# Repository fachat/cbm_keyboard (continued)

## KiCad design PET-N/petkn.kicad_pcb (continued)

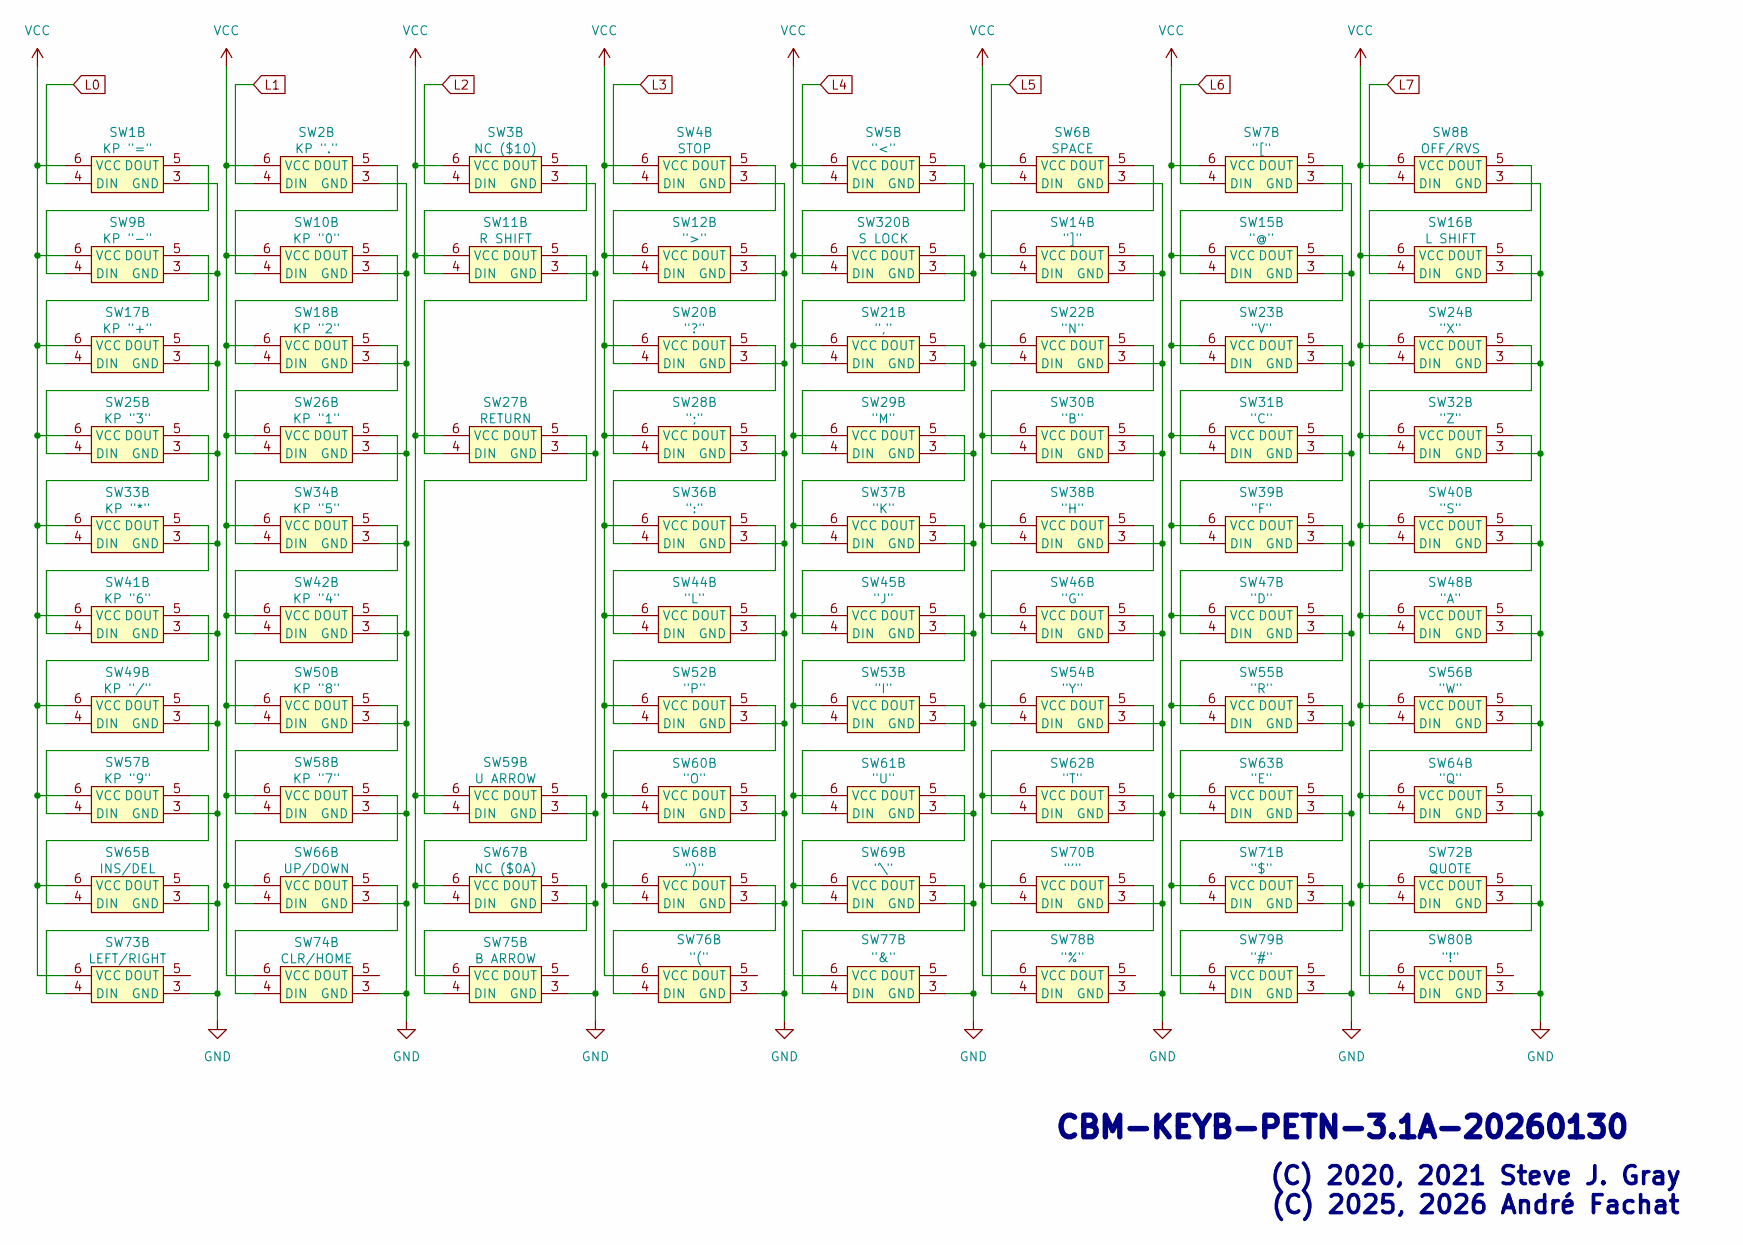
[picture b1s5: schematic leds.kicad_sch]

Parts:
SW1: KP "="; SW_Cherry_MX_1.00u_PCB_with_RGB_LED
SW2: KP "."; SW_Cherry_MX_1.00u_PCB_with_RGB_LED
SW3: NC ($10); SW_Cherry_MX_1.25u_PCB_with_RGB_LED
SW4: STOP; SW_Cherry_MX_1.00u_PCB_with_RGB_LED
SW5: "<"; SW_Cherry_MX_1.00u_PCB_with_RGB_LED
SW6: SPACE; SW_Cherry_MX_6.25u_PCB_with_RGB_LED
SW7: "["; SW_Cherry_MX_1.00u_PCB_with_RGB_LED
SW8: OFF/RVS; SW_Cherry_MX_1.50u_PCB_with_RGB_LED
SW9: KP "-"; SW_Cherry_MX_1.00u_PCB_with_RGB_LED
SW10: KP "0"; SW_Cherry_MX_1.00u_PCB_with_RGB_LED
SW11: R SHIFT; SW_Cherry_MX_2.00u_PCB_with_RGB_LED
SW12: ">"; SW_Cherry_MX_1.00u_PCB_with_RGB_LED
SW14: "]"; SW_Cherry_MX_1.00u_PCB_with_RGB_LED
SW15: "@"; SW_Cherry_MX_1.00u_PCB_with_RGB_LED
SW16: L SHIFT; SW_Cherry_MX_2.00u_PCB_with_RGB_LED
SW17: KP "+"; SW_Cherry_MX_1.00u_PCB_with_RGB_LED
SW18: KP "2"; SW_Cherry_MX_1.00u_PCB_with_RGB_LED
SW20: "?"; SW_Cherry_MX_1.00u_PCB_with_RGB_LED
SW21: ","; SW_Cherry_MX_1.00u_PCB_with_RGB_LED
SW22: "N"; SW_Cherry_MX_1.00u_PCB_with_RGB_LED
SW23: "V"; SW_Cherry_MX_1.00u_PCB_with_RGB_LED
SW24: "X"; SW_Cherry_MX_1.00u_PCB_with_RGB_LED
SW25: KP "3"; SW_Cherry_MX_1.00u_PCB_with_RGB_LED
SW26: KP "1"; SW_Cherry_MX_1.00u_PCB_with_RGB_LED
SW27: RETURN; SW_Cherry_MX_1.50u_PCB_with_RGB_LED
SW28: ";"; SW_Cherry_MX_1.00u_PCB_with_RGB_LED
SW29: "M"; SW_Cherry_MX_1.00u_PCB_with_RGB_LED
SW30: "B"; SW_Cherry_MX_1.00u_PCB_with_RGB_LED
SW31: "C"; SW_Cherry_MX_1.00u_PCB_with_RGB_LED
SW32: "Z"; SW_Cherry_MX_1.00u_PCB_with_RGB_LED
SW33: KP "*"; SW_Cherry_MX_1.00u_PCB_with_RGB_LED
SW34: KP "5"; SW_Cherry_MX_1.00u_PCB_with_RGB_LED
SW36: ":"; SW_Cherry_MX_1.00u_PCB_with_RGB_LED
SW37: "K"; SW_Cherry_MX_1.00u_PCB_with_RGB_LED
SW38: "H"; SW_Cherry_MX_1.00u_PCB_with_RGB_LED
SW39: "F"; SW_Cherry_MX_1.00u_PCB_with_RGB_LED
SW40: "S"; SW_Cherry_MX_1.00u_PCB_with_RGB_LED
SW41: KP "6"; SW_Cherry_MX_1.00u_PCB_with_RGB_LED
SW42: KP "4"; SW_Cherry_MX_1.00u_PCB_with_RGB_LED
SW44: "L"; SW_Cherry_MX_1.00u_PCB_with_RGB_LED
SW45: "J"; SW_Cherry_MX_1.00u_PCB_with_RGB_LED
SW46: "G"; SW_Cherry_MX_1.00u_PCB_with_RGB_LED
SW47: "D"; SW_Cherry_MX_1.00u_PCB_with_RGB_LED
SW48: "A"; SW_Cherry_MX_1.00u_PCB_with_RGB_LED
SW49: KP "/"; SW_Cherry_MX_1.00u_PCB_with_RGB_LED
SW50: KP "8"; SW_Cherry_MX_1.00u_PCB_with_RGB_LED
SW52: "P"; SW_Cherry_MX_1.00u_PCB_with_RGB_LED
SW53: "I"; SW_Cherry_MX_1.00u_PCB_with_RGB_LED
SW54: "Y"; SW_Cherry_MX_1.00u_PCB_with_RGB_LED
SW55: "R"; SW_Cherry_MX_1.00u_PCB_with_RGB_LED
SW56: "W"; SW_Cherry_MX_1.00u_PCB_with_RGB_LED
SW57: KP "9"; SW_Cherry_MX_1.00u_PCB_with_RGB_LED
SW58: KP "7"; SW_Cherry_MX_1.00u_PCB_with_RGB_LED
SW59: U ARROW; SW_Cherry_MX_1.00u_PCB_with_RGB_LED
SW60: "O"; SW_Cherry_MX_1.00u_PCB_with_RGB_LED
SW61: "U"; SW_Cherry_MX_1.00u_PCB_with_RGB_LED
SW62: "T"; SW_Cherry_MX_1.00u_PCB_with_RGB_LED
SW63: "E"; SW_Cherry_MX_1.00u_PCB_with_RGB_LED
SW64: "Q"; SW_Cherry_MX_1.00u_PCB_with_RGB_LED
SW65: INS/DEL; SW_Cherry_MX_1.00u_PCB_with_RGB_LED
SW66: UP/DOWN; SW_Cherry_MX_1.00u_PCB_with_RGB_LED
SW67: NC ($0A); SW_Cherry_MX_1.50u_PCB_with_RGB_LED
SW68: ")"; SW_Cherry_MX_1.00u_PCB_with_RGB_LED
SW69: "\"; SW_Cherry_MX_1.00u_PCB_with_RGB_LED
SW70: "'"; SW_Cherry_MX_1.00u_PCB_with_RGB_LED
SW71: "$"; SW_Cherry_MX_1.00u_PCB_with_RGB_LED
SW72: QUOTE; SW_Cherry_MX_1.00u_PCB_with_RGB_LED
SW73: LEFT/RIGHT; SW_Cherry_MX_1.00u_PCB_with_RGB_LED
SW74: CLR/HOME; SW_Cherry_MX_1.00u_PCB_with_RGB_LED
SW75: B ARROW; SW_Cherry_MX_1.00u_PCB_with_RGB_LED
SW76: "("; SW_Cherry_MX_1.00u_PCB_with_RGB_LED
SW77: "&"; SW_Cherry_MX_1.00u_PCB_with_RGB_LED
SW78: "%"; SW_Cherry_MX_1.00u_PCB_with_RGB_LED
SW79: "#"; SW_Cherry_MX_1.00u_PCB_with_RGB_LED
SW80: "!"; SW_Cherry_MX_1.00u_PCB_with_RGB_LED
SW320: S LOCK; SW_Cherry_MX_1.50u_PCB_with_RGB_LED

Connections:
GND: SW1.3 (GND), SW2.3 (GND), SW3.3 (GND), SW4.3 (GND), SW5.3 (GND), SW6.3 (GND), SW7.3 (GND), SW8.3 (GND), SW9.3 (GND), SW10.3 (GND), SW11.3 (GND), SW12.3 (GND), SW14.3 (GND), SW15.3 (GND), SW16.3 (GND), SW17.3 (GND), SW18.3 (GND), SW20.3 (GND), SW21.3 (GND), SW22.3 (GND), SW23.3 (GND), SW24.3 (GND), SW25.3 (GND), SW26.3 (GND), SW27.3 (GND), SW28.3 (GND), SW29.3 (GND), SW30.3 (GND), SW31.3 (GND), SW32.3 (GND), SW33.3 (GND), SW34.3 (GND), SW36.3 (GND), SW37.3 (GND), SW38.3 (GND), SW39.3 (GND), SW40.3 (GND), SW41.3 (GND), SW42.3 (GND), SW44.3 (GND), SW45.3 (GND), SW46.3 (GND), SW47.3 (GND), SW48.3 (GND), SW49.3 (GND), SW50.3 (GND), SW52.3 (GND), SW53.3 (GND), SW54.3 (GND), SW55.3 (GND), SW56.3 (GND), SW57.3 (GND), SW58.3 (GND), SW59.3 (GND), SW60.3 (GND), SW61.3 (GND), SW62.3 (GND), SW63.3 (GND), SW64.3 (GND), SW65.3 (GND), SW66.3 (GND), SW67.3 (GND), SW68.3 (GND), SW69.3 (GND), SW70.3 (GND), SW71.3 (GND), SW72.3 (GND), SW73.3 (GND), SW74.3 (GND), SW75.3 (GND), SW76.3 (GND), SW77.3 (GND), SW78.3 (GND), SW79.3 (GND), SW80.3 (GND), SW320.3 (GND); also elsewhere on the board
L0: SW1.4 (DIN); also elsewhere on the board
L1: SW2.4 (DIN); also elsewhere on the board
L2: SW3.4 (DIN); also elsewhere on the board
L3: SW4.4 (DIN); also elsewhere on the board
L4: SW5.4 (DIN); also elsewhere on the board
L5: SW6.4 (DIN); also elsewhere on the board
L6: SW7.4 (DIN); also elsewhere on the board
L7: SW8.4 (DIN); also elsewhere on the board
unnamed: SW1.5 (DOUT), SW9.4 (DIN)
unnamed: SW2.5 (DOUT), SW10.4 (DIN)
unnamed: SW10.5 (DOUT), SW18.4 (DIN)
unnamed: SW3.5 (DOUT), SW11.4 (DIN)
unnamed: SW11.5 (DOUT), SW27.4 (DIN)
unnamed: SW4.5 (DOUT), SW12.4 (DIN)
unnamed: SW12.5 (DOUT), SW20.4 (DIN)
unnamed: SW6.5 (DOUT), SW14.4 (DIN)
unnamed: SW14.5 (DOUT), SW22.4 (DIN)
unnamed: SW7.5 (DOUT), SW15.4 (DIN)
unnamed: SW15.5 (DOUT), SW23.4 (DIN)
unnamed: SW8.5 (DOUT), SW16.4 (DIN)
unnamed: SW16.5 (DOUT), SW24.4 (DIN)
unnamed: SW9.5 (DOUT), SW17.4 (DIN)
unnamed: SW17.5 (DOUT), SW25.4 (DIN)
unnamed: SW18.5 (DOUT), SW26.4 (DIN)
unnamed: SW20.5 (DOUT), SW28.4 (DIN)
unnamed: SW21.4 (DIN), SW320.5 (DOUT)
unnamed: SW21.5 (DOUT), SW29.4 (DIN)
unnamed: SW22.5 (DOUT), SW30.4 (DIN)
unnamed: SW23.5 (DOUT), SW31.4 (DIN)
unnamed: SW24.5 (DOUT), SW32.4 (DIN)
unnamed: SW25.5 (DOUT), SW33.4 (DIN)
unnamed: SW26.5 (DOUT), SW34.4 (DIN)
unnamed: SW27.5 (DOUT), SW59.4 (DIN)
unnamed: SW28.5 (DOUT), SW36.4 (DIN)
unnamed: SW29.5 (DOUT), SW37.4 (DIN)
unnamed: SW30.5 (DOUT), SW38.4 (DIN)
unnamed: SW31.5 (DOUT), SW39.4 (DIN)
unnamed: SW32.5 (DOUT), SW40.4 (DIN)
unnamed: SW33.5 (DOUT), SW41.4 (DIN)
unnamed: SW34.5 (DOUT), SW42.4 (DIN)
unnamed: SW36.5 (DOUT), SW44.4 (DIN)
unnamed: SW37.5 (DOUT), SW45.4 (DIN)
unnamed: SW38.5 (DOUT), SW46.4 (DIN)
unnamed: SW39.5 (DOUT), SW47.4 (DIN)
unnamed: SW40.5 (DOUT), SW48.4 (DIN)
unnamed: SW41.5 (DOUT), SW49.4 (DIN)
unnamed: SW42.5 (DOUT), SW50.4 (DIN)
unnamed: SW44.5 (DOUT), SW52.4 (DIN)
unnamed: SW45.5 (DOUT), SW53.4 (DIN)
unnamed: SW46.5 (DOUT), SW54.4 (DIN)
unnamed: SW47.5 (DOUT), SW55.4 (DIN)
unnamed: SW48.5 (DOUT), SW56.4 (DIN)
unnamed: SW49.5 (DOUT), SW57.4 (DIN)
unnamed: SW50.5 (DOUT), SW58.4 (DIN)
unnamed: SW52.5 (DOUT), SW60.4 (DIN)
unnamed: SW53.5 (DOUT), SW61.4 (DIN)
unnamed: SW54.5 (DOUT), SW62.4 (DIN)
unnamed: SW55.5 (DOUT), SW63.4 (DIN)
unnamed: SW56.5 (DOUT), SW64.4 (DIN)
unnamed: SW57.5 (DOUT), SW65.4 (DIN)
unnamed: SW58.5 (DOUT), SW66.4 (DIN)
unnamed: SW59.5 (DOUT), SW67.4 (DIN)
unnamed: SW60.5 (DOUT), SW68.4 (DIN)
unnamed: SW61.5 (DOUT), SW69.4 (DIN)
unnamed: SW62.5 (DOUT), SW70.4 (DIN)
unnamed: SW63.5 (DOUT), SW71.4 (DIN)
unnamed: SW64.5 (DOUT), SW72.4 (DIN)
unnamed: SW65.5 (DOUT), SW73.4 (DIN)
unnamed: SW66.5 (DOUT), SW74.4 (DIN)
unnamed: SW67.5 (DOUT), SW75.4 (DIN)
unnamed: SW68.5 (DOUT), SW76.4 (DIN)
unnamed: SW69.5 (DOUT), SW77.4 (DIN)
unnamed: SW70.5 (DOUT), SW78.4 (DIN)
unnamed: SW71.5 (DOUT), SW79.4 (DIN)
unnamed: SW72.5 (DOUT), SW80.4 (DIN)
unnamed: SW5.5 (DOUT), SW320.4 (DIN)
VCC: SW1.6 (VCC), SW2.6 (VCC), SW3.6 (VCC), SW4.6 (VCC), SW5.6 (VCC), SW6.6 (VCC), SW7.6 (VCC), SW8.6 (VCC), SW9.6 (VCC), SW10.6 (VCC), SW11.6 (VCC), SW12.6 (VCC), SW14.6 (VCC), SW15.6 (VCC), SW16.6 (VCC), SW17.6 (VCC), SW18.6 (VCC), SW20.6 (VCC), SW21.6 (VCC), SW22.6 (VCC), SW23.6 (VCC), SW24.6 (VCC), SW25.6 (VCC), SW26.6 (VCC), SW27.6 (VCC), SW28.6 (VCC), SW29.6 (VCC), SW30.6 (VCC), SW31.6 (VCC), SW32.6 (VCC), SW33.6 (VCC), SW34.6 (VCC), SW36.6 (VCC), SW37.6 (VCC), SW38.6 (VCC), SW39.6 (VCC), SW40.6 (VCC), SW41.6 (VCC), SW42.6 (VCC), SW44.6 (VCC), SW45.6 (VCC), SW46.6 (VCC), SW47.6 (VCC), SW48.6 (VCC), SW49.6 (VCC), SW50.6 (VCC), SW52.6 (VCC), SW53.6 (VCC), SW54.6 (VCC), SW55.6 (VCC), SW56.6 (VCC), SW57.6 (VCC), SW58.6 (VCC), SW59.6 (VCC), SW60.6 (VCC), SW61.6 (VCC), SW62.6 (VCC), SW63.6 (VCC), SW64.6 (VCC), SW65.6 (VCC), SW66.6 (VCC), SW67.6 (VCC), SW68.6 (VCC), SW69.6 (VCC), SW70.6 (VCC), SW71.6 (VCC), SW72.6 (VCC), SW73.6 (VCC), SW74.6 (VCC), SW75.6 (VCC), SW76.6 (VCC), SW77.6 (VCC), SW78.6 (VCC), SW79.6 (VCC), SW80.6 (VCC), SW320.6 (VCC); also elsewhere on the board

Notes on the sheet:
CBM-KEYB-PETN-3.1A-20260130
(C) 2020, 2021 Steve J. Gray (C) 2025, 2026 André Fachat

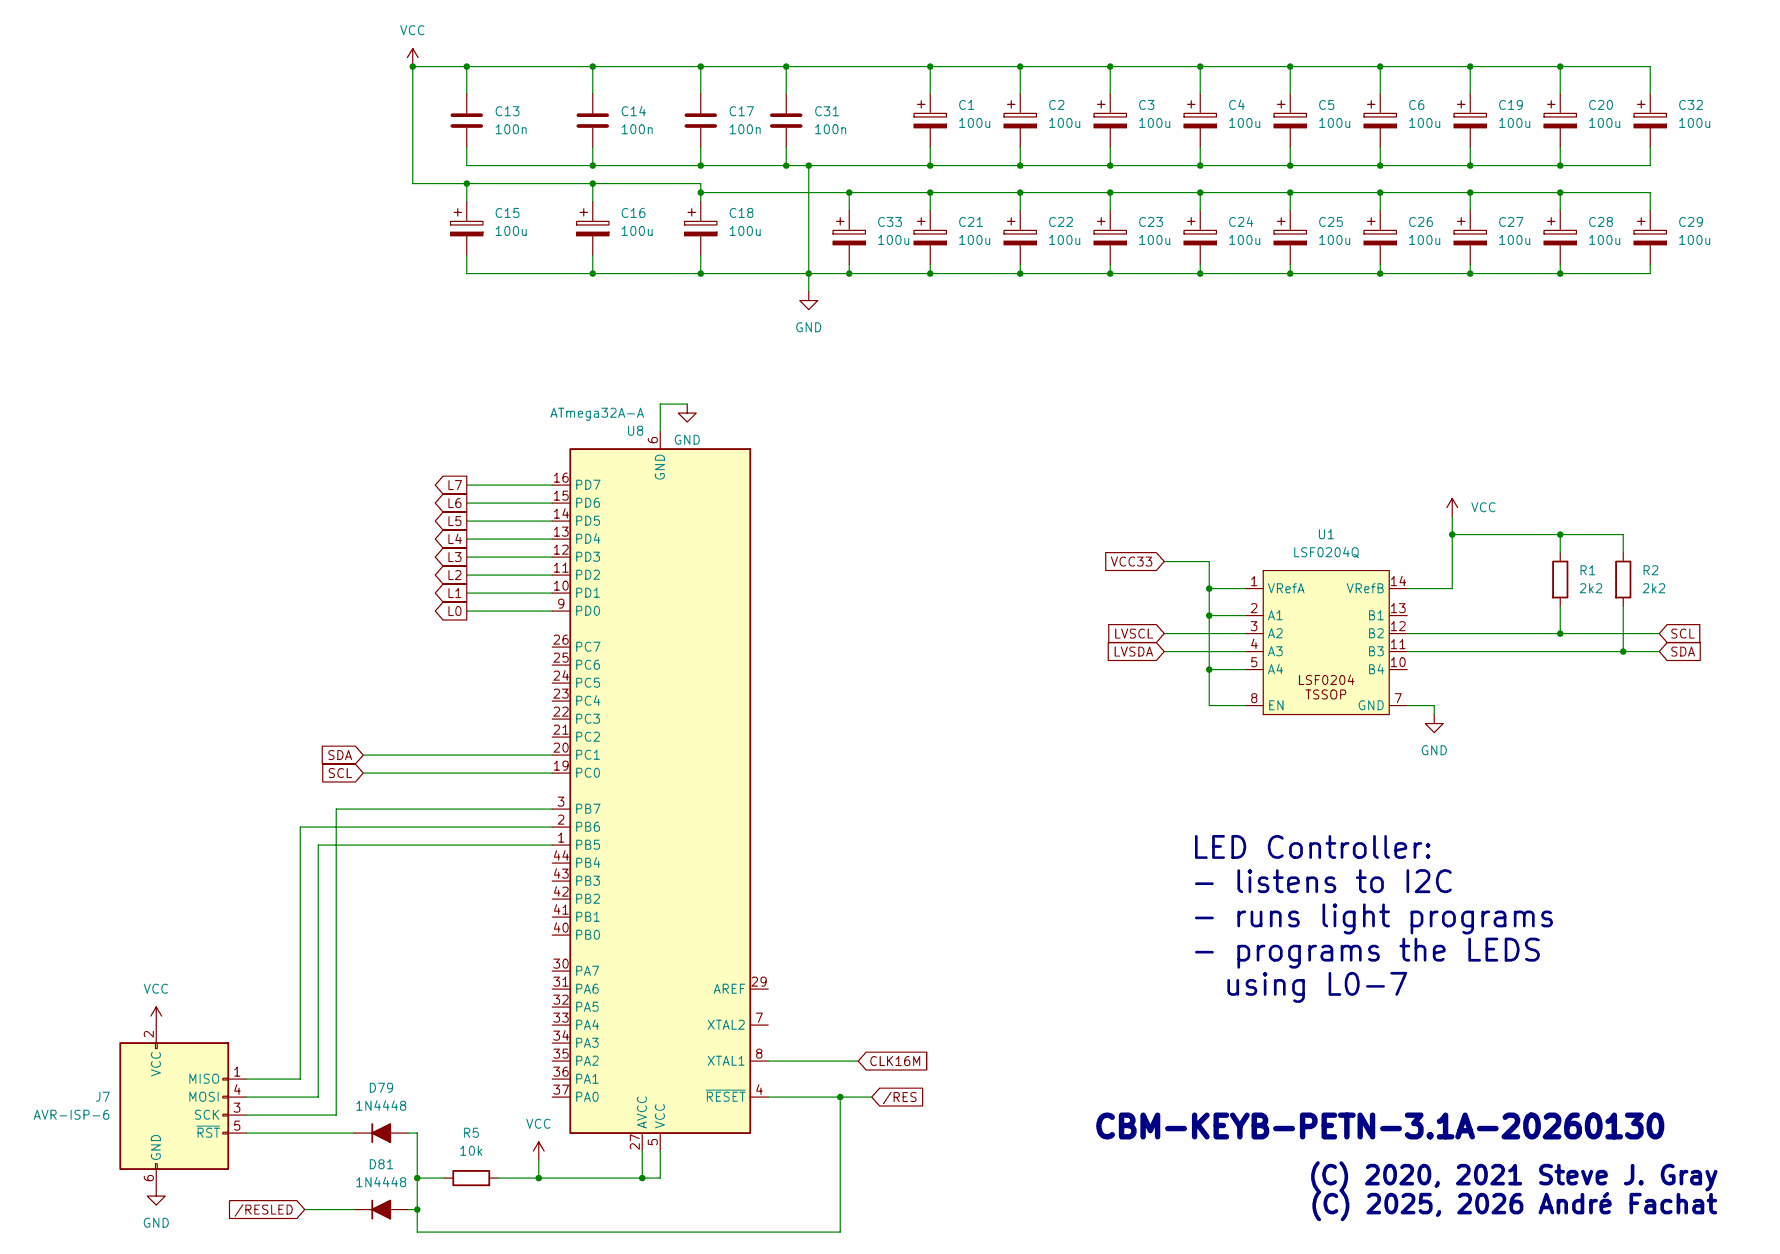
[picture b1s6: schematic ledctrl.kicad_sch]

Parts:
C1, C2, C3, C4, C5, C6, C15, C16, C18, C19, C20, C21, C22, C23, C24, C25, C26, C27, C28, C29, C32, C33: 100u; C_1206_3216Metric_Pad1.33x1.80mm_HandSolder; LCSC C15008
C13, C14, C17, C31: 100n; C_0805_2012Metric_Pad1.18x1.45mm_HandSolder; LCSC C14663
D79, D81: 1N4448; D_SOD-323_HandSoldering
J7: AVR-ISP-6; IDC-Header_2x03_P2.54mm_Vertical; LCSC C5372863
R1, R2: 2k2; R_0603_1608Metric
R5: 10k; R_0603_1608Metric
U1: LSF0204Q; TSSOP-14_4.4x5mm_P0.65mm; LCSC C2677502
U8: ATmega32A-A; TQFP-44_10x10mm_P0.8mm; LCSC C5659

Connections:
CLK16M: U8.8 (XTAL1); also elsewhere on the board
GND: C1.2, C2.2, C3.2, C4.2, C5.2, C6.2, C13.2, C14.2, C15.2, C16.2, C17.2, C18.2, C19.2, C20.2, C21.2, C22.2, C23.2, C24.2, C25.2, C26.2, C27.2, C28.2, C29.2, C31.2, C32.2, C33.2, J7.6 (GND), U1.7 (GND), U8.6 (GND), U8.18 (GND), U8.28 (GND), U8.39 (GND); also elsewhere on the board
L0: U8.9 (PD0); also elsewhere on the board
L1: U8.10 (PD1); also elsewhere on the board
L2: U8.11 (PD2); also elsewhere on the board
L3: U8.12 (PD3); also elsewhere on the board
L4: U8.13 (PD4); also elsewhere on the board
L5: U8.14 (PD5); also elsewhere on the board
L6: U8.15 (PD6); also elsewhere on the board
L7: U8.16 (PD7); also elsewhere on the board
LVSCL: U1.3 (A2); also elsewhere on the board
LVSDA: U1.4 (A3); also elsewhere on the board
unnamed: D79.1 (K), J7.5 (~RST)
unnamed: J7.1 (MISO), U8.2 (PB6)
unnamed: J7.4 (MOSI), U8.1 (PB5)
unnamed: J7.3 (SCK), U8.3 (PB7)
SCL: R1.2, U1.12 (B2), U8.19 (PC0); also elsewhere on the board
SDA: R2.2, U1.11 (B3), U8.20 (PC1); also elsewhere on the board
VCC: C1.1, C2.1, C3.1, C4.1, C5.1, C6.1, C13.1, C14.1, C15.1, C16.1, C17.1, C18.1, C19.1, C20.1, C21.1, C22.1, C23.1, C24.1, C25.1, C26.1, C27.1, C28.1, C29.1, C31.1, C32.1, C33.1, J7.2 (VCC), R1.1, R2.1, R5.2, U1.14 (VRefB), U8.5 (VCC), U8.17 (VCC), U8.27 (AVCC), U8.38 (VCC); also elsewhere on the board
VCC33: U1.1 (VRefA), U1.2 (A1), U1.5 (A4), U1.8 (EN); also elsewhere on the board
cR1: D79.2 (A), D81.2 (A), R5.1, U8.4 (~RESET); also elsewhere on the board
/RESLED: D81.1 (K); also elsewhere on the board

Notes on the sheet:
(C) 2020, 2021 Steve J. Gray (C) 2025, 2026 André Fachat
CBM-KEYB-PETN-3.1A-20260130
LED Controller: - listens to I2C - runs light programs - programs the LEDS using L0-7

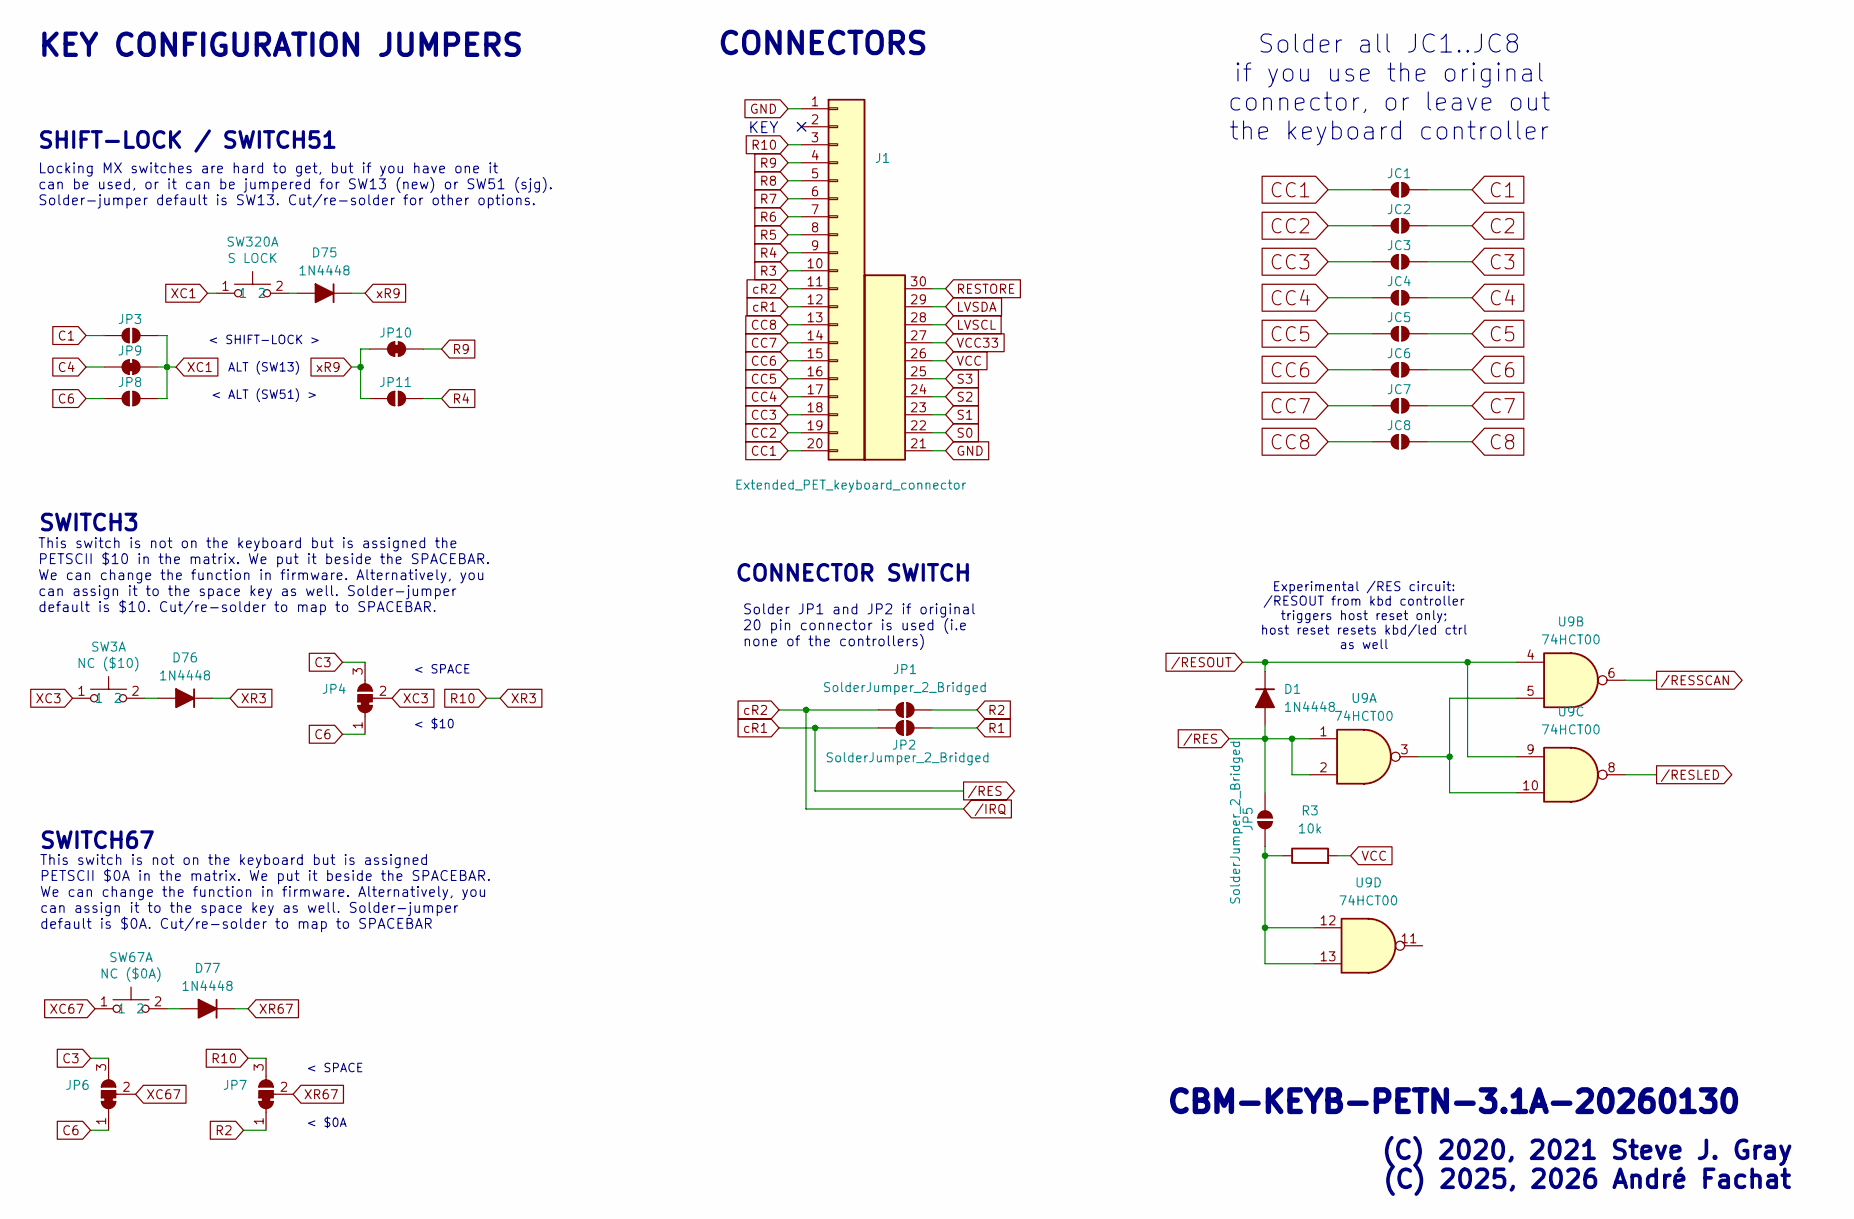
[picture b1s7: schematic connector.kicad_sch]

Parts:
D1, D75, D76, D77: 1N4448; D_SOD-323_HandSoldering
J1: Extended_PET_keyboard_connector; PET_Extended_Keyboard_Connector
JC1, JC2, JC3, JC4, JC5, JC6, JC7, JC8: SolderJumper_2_Bridged; SolderJumper-2_P1.3mm_Open_RoundedPad1.0x1.5mm
JP1, JP2, JP3, JP5, JP8, JP11: SolderJumper_2_Bridged; SolderJumper-2_P1.3mm_Open_RoundedPad1.0x1.5mm
JP4, JP6, JP7: SolderJumper_3_Bridged12; SolderJumper-3_P1.3mm_Bridged12_RoundedPad1.0x1.5mm_NumberL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
JP9, JP10: SolderJumper_2_Bridged; SolderJumper-2_P1.3mm_Bridged_RoundedPad1.0x1.5mm
R3: 10k; R_0603_1608Metric
SW3: NC ($10); SW_Cherry_MX_1.25u_PCB_with_RGB_LED
SW67: NC ($0A); SW_Cherry_MX_1.50u_PCB_with_RGB_LED
SW320: S LOCK; SW_Cherry_MX_1.50u_PCB_with_RGB_LED
U9: 74HCT00; SOIC-14_3.9x8.7mm_P1.27mm

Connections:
C1: JC1.2 (B), JP3.1 (A); also elsewhere on the board
C2: JC2.2 (B); also elsewhere on the board
C3: JC3.2 (B), JP4.3 (B), JP6.3 (B); also elsewhere on the board
C4: JC4.2 (B), JP9.1 (A); also elsewhere on the board
C5: JC5.2 (B); also elsewhere on the board
C6: JC6.2 (B), JP4.1 (A), JP6.1 (A), JP8.1 (A); also elsewhere on the board
C7: JC7.2 (B); also elsewhere on the board
C8: JC8.2 (B); also elsewhere on the board
CC1: J1.20 (C1), JC1.1 (A); also elsewhere on the board
CC2: J1.19 (C2), JC2.1 (A); also elsewhere on the board
CC3: J1.18 (C3), JC3.1 (A); also elsewhere on the board
CC4: J1.17 (C4), JC4.1 (A); also elsewhere on the board
CC5: J1.16 (C5), JC5.1 (A); also elsewhere on the board
CC6: J1.15 (C6), JC6.1 (A); also elsewhere on the board
CC7: J1.14 (C7), JC7.1 (A); also elsewhere on the board
CC8: J1.13 (C8), JC8.1 (A); also elsewhere on the board
GND: J1.1 (GND), J1.21 (GND); also elsewhere on the board
LVSCL: J1.28 (SCL); also elsewhere on the board
LVSDA: J1.29 (SCA); also elsewhere on the board
unnamed: D75.2 (A), SW320.2
unnamed: D76.2 (A), SW3.2
unnamed: D77.2 (A), SW67.2
unnamed: JP5.2 (B), R3.1, U9.12, U9.13
unnamed: U9.3, U9.5, U9.10
R1: JP2.2 (B); also elsewhere on the board
R2: JP1.2 (B), JP7.1 (A); also elsewhere on the board
R3: J1.10 (R3); also elsewhere on the board
R4: J1.9 (R4), JP11.2 (B); also elsewhere on the board
R5: J1.8 (R5); also elsewhere on the board
R6: J1.7 (R6); also elsewhere on the board
R7: J1.6 (R7); also elsewhere on the board
R8: J1.5 (R8); also elsewhere on the board
R9: J1.4 (R9), JP10.2 (B); also elsewhere on the board
R10: D76.1 (K), J1.3 (R10), JP7.3 (B); also elsewhere on the board
RESTORE: J1.30 (RESTORE)
S0: J1.22 (S0); also elsewhere on the board
S1: J1.23 (S1); also elsewhere on the board
S2: J1.24 (S2); also elsewhere on the board
S3: J1.25 (S3); also elsewhere on the board
VCC: J1.26 (VCC5), R3.2; also elsewhere on the board
VCC33: J1.27 (VCC33); also elsewhere on the board
XC1: JP3.2 (B), JP8.2 (B), JP9.2 (B), SW320.1
XC3: JP4.2 (C), SW3.1
XC67: JP6.2 (C), SW67.1
XR67: D77.1 (K), JP7.2 (C)
cR1: D1.2 (A), J1.12 (R1), JP2.1 (A), JP5.1 (A), U9.1, U9.2; also elsewhere on the board
cR2: J1.11 (R2), JP1.1 (A)
xR9: D75.1 (K), JP10.1 (A), JP11.1 (A)
/RESLED: U9.8; also elsewhere on the board
/RESOUT: D1.1 (K), U9.4, U9.9; also elsewhere on the board
/RESSCAN: U9.6; also elsewhere on the board

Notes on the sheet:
Solder all JC1..JC8 if you use the original connector, or leave out the keyboard controller
CONNECTORS
CBM-KEYB-PETN-3.1A-20260130
Locking MX switches are hard to get, but if you have one it can be used, or it can be jumpered for SW13 (new) or SW51 (sjg). Solder-jumper default is SW13. Cut/re-solder for other options.
Solder JP1 and JP2 if original 20 pin connector is used (i.e none of the controllers)
This switch is not on the keyboard but is assigned PETSCII $0A in the matrix. We put it beside the SPACEBAR. We can change the function in firmware. Alternatively, you can assign it to the space key as well. Solder-jumper default is $0A. Cut/re-solder to map to SPACEBAR
< SHIFT-LOCK > ALT (SW13) < ALT (SW51) >
SWITCH67
KEY CONFIGURATION JUMPERS
< SPACE < $10
(C) 2020, 2021 Steve J. Gray (C) 2025, 2026 André Fachat
SHIFT-LOCK / SWITCH51
Experimental /RES circuit: /RESOUT from kbd controller triggers host reset only; host reset resets kbd/led ctrl as well
< SPACE < $0A
This switch is not on the keyboard but is assigned the PETSCII $10 in the matrix. We put it beside the SPACEBAR. We can change the function in firmware. Alternatively, you can assign it to the space key as well. Solder-jumper default is $10. Cut/re-solder to map to SPACEBAR.
KEY
SWITCH3
CONNECTOR SWITCH

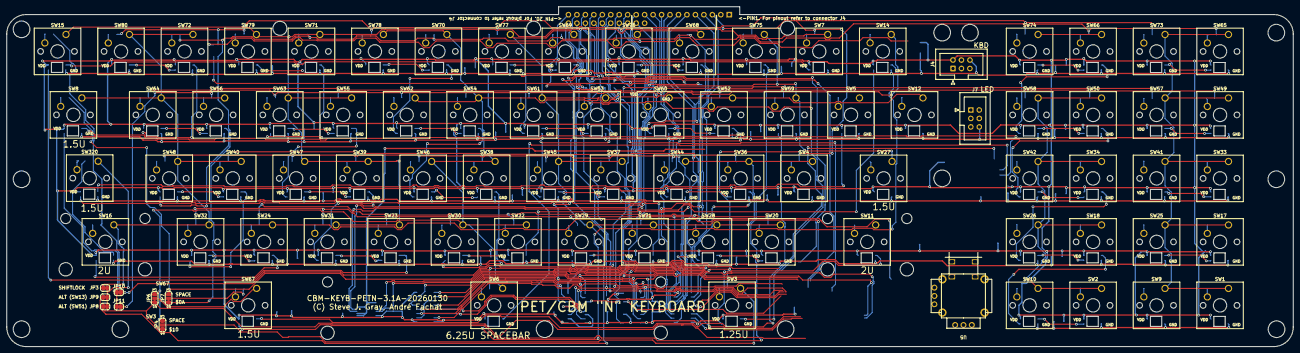
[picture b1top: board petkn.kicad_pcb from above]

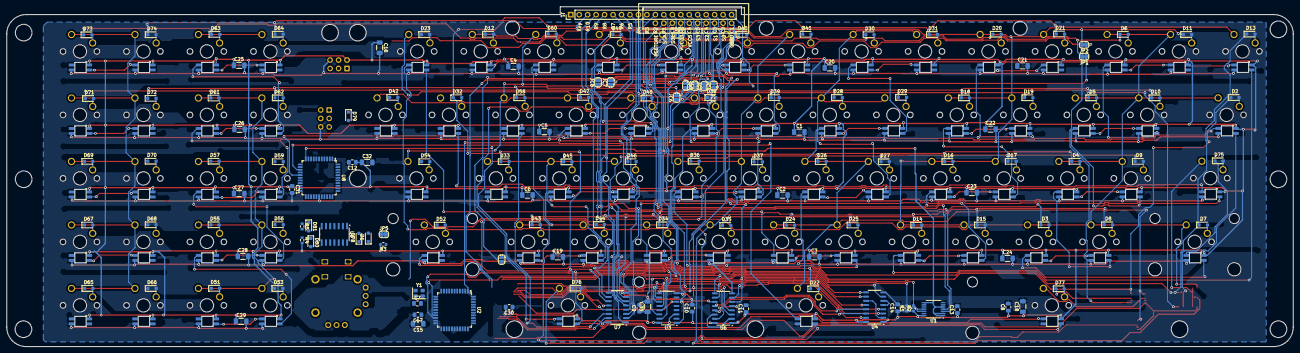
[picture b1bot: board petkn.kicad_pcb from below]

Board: 2 copper layers, 386.1 x 102.0 mm, 227 parts (140 on the bottom side), 227 nets.

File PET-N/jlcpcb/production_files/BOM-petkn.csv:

Comment,Designator,Footprint,LCSC,Quantity
100n,"C10,C11,C12,C13,C14,C17,C30,C31,C7,C8,C9",C_0805_2012Metric_Pad1.18x1.45mm_HandSolder,C14663,11
100u,"C1,C15,C16,C18,C19,C2,C20,C21,C22,C23,C24,C25,C26,C27,C28,C29,C3,C32,C33,C4,C5,C6",C_1206_3216Metric_Pad1.33x1.80mm_HandSolder,C15008,22
1N4448,D1,D_SOD-323_HandSoldering,C2128,1
LSF0204Q,U1,TSSOP-14_4.4x5mm_P0.65mm,C2677502,1
~,U5,THB Miniature Thumbstick THB001P,C2685355,1
"KP ""=""","SW1,SW10,SW11,SW12,SW14,SW15,SW16,SW17,SW18,SW2,SW20,SW21,SW22,SW23,SW24,SW25,SW26,SW27,SW28,SW29,SW3,SW30,SW31,SW32,SW320,SW33,SW34,SW36,SW37,SW38,SW39,SW4,SW40,SW41,SW42,SW44,SW45,SW46,SW47,SW48,SW49,SW5,SW50,SW52,SW53,SW54,SW55,SW56,SW57,SW58,SW59,SW6,SW60,SW61,SW62,SW63,SW64,SW65,SW66,SW67,SW68,SW69,SW7,SW70,SW71,SW72,SW73,SW74,SW75,SW76,SW77,SW78,SW79,SW8,SW80,SW9",SW_Cherry_MX_1.00u_PCB_with_RGB_LED,C5149201,76
ASE-xxxMHz,Y1,Oscillator_SMD_Abracon_ASE-4Pin_3.2x2.5mm,C5158780,1
AVR-ISP-6,"J4,J7",IDC-Header_2x03_P2.54mm_Vertical,C5372863,2
ATmega32A-A,"U2,U8",TQFP-44_10x10mm_P0.8mm,C5659,2
74HCT85,U3,SO-16_3.9x9.9mm_P1.27mm,C5953,1
74LS145,U7,SO-16_3.9x9.9mm_P1.27mm,C60829,1
74LS174,"U4,U6",SO-16_3.9x9.9mm_P1.27mm,C6828,2
Extended_PET_keyboard_connector,J1,PET_Extended_Keyboard_Connector,,1
